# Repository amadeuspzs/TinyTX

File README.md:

# TinyTX

This repo picks up on the work on Nathan Chantrell, sadly R.I.P. late 2020.

* Nathan's website [via Archive.org](https://web.archive.org/web/20150202220320/http://nathan.chantrell.net/tinytx-wireless-sensor/)
* Nathan's [TinyTX repo on Github](https://github.com/nathanchantrell/TinyTX)
* Archive of [TinyTX3 hardware](TinyTX3/)

## Motivation

Since Nathan created TinyTX, both chips have evolved:

1. RFM12B -> [RFM69](https://www.hoperf.com/modules/rf_transceiver/index.html)
2. ATtiny84 -> ATtiny 0,1 series e.g. [ATtiny1614](https://ww1.microchip.com/downloads/en/DeviceDoc/ATtiny1614-16-17-DataSheet-DS40002204A.pdf)

## High level design

This project will create a TinyTX4 using:

1. RFM69HW
2. ATtiny1614
3. lowpowerlab's [RFM69](https://github.com/lowpowerlab/rfm69) library

And release all hardware and software in this repository.

## Radio module choice

Here is a comparison of [RFM69](https://www.hoperf.com/modules/rf_transceiver/index.html) variants:

Variant|Output (dBm)|Pinout|Size (mm)
---|---|---|---
RFM69[**W**](https://www.hoperf.com/modules/rf_transceiver/RFM69W.html)|13|RFM69W|19.7 x 16
RFM69[**CW**](https://www.hoperf.com/modules/rf_transceiver/RFM69C.html)|13|RFM69CW|16 x 16
RFM69[**HW**](https://www.hoperf.com/%20modules/rf_transceiver/RFM69HW.html)|20|RFM69W|19.7 x 16
RFM69[**HCW**](https://www.hoperf.com/modules/rf_transceiver/RFM69HCW.html)|20|RFM69HCW|16 x 16

i.e. RFM69W and RFM69HW share pinout, but are larger (19.7&nbsp;x&nbsp;16)mm vs the RFMCW and RFMHCW (16&nbsp;x&nbsp;16)mm.

For interoperability between normal and high-power modules, we'll go with the **RFM69(H)W** modules.

## Hardware versions

* [TinyTX4](hardware/TinyTX4) (monopole and SMA)

## Software

See [software](software/) page.

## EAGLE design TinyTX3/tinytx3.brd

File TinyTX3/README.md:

# TinyTX3 Hardware

Archived from Nathan's website [via Archive.org](https://web.archive.org/web/20150202220320/http://nathan.chantrell.net/tinytx-wireless-sensor/):

## Schematic

* [Eagle file](tinytx3.sch)
* [KiCad files](KiCad/)

## Board

* [Eagle file](tinytx3.brd)
* [KiCad files](KiCad/)

## Case

* [OpenSCAD](TinyTX_Case.scad)

## Implementation

### Pinout

### AA implementation

### LiPo implementation

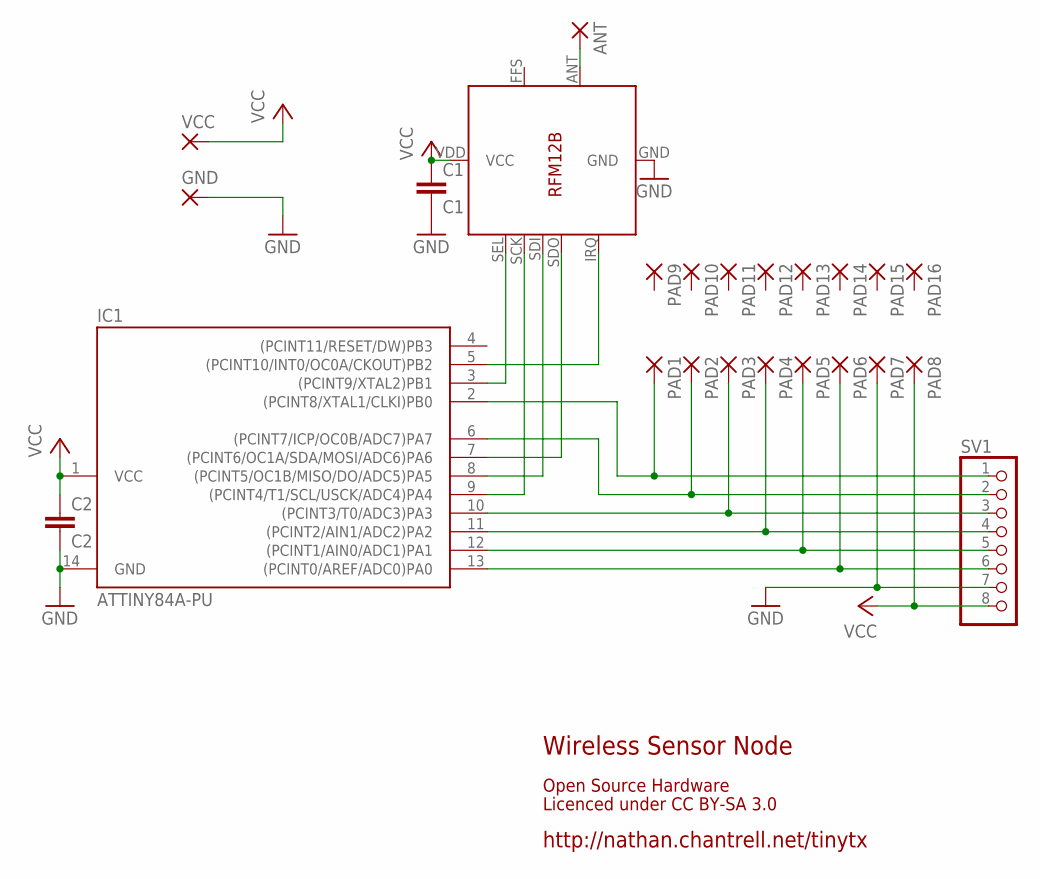
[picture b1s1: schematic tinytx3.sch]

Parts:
ANT: 1,6/0,8
C1: C1; C025-025X050
C2: C2; C025-025X050
GND: 2,15/1,0
IC1: ATTINY84A-PU; DIL14
PAD1, PAD2, PAD3, PAD4, PAD5, PAD6, PAD7, PAD8, PAD9, PAD10, PAD11, PAD12, PAD13, PAD14, PAD15, PAD16: 1,6/0,9
SV1: PINHD-1X8; 1X08
U$1: RFM12B
VCC: 2,15/1,0

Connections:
GND: C1.2, C2.2, GND.1, IC1.14 (GND), PAD7.1, SV1.7, U$1.GND
unnamed: IC1.3 ((PCINT9/XTAL2)PB1), U$1.SEL
unnamed: IC1.5 ((PCINT10/INT0/OC0A/CKOUT)PB2), U$1.IRQ
unnamed: IC1.8 ((PCINT5/OC1B/MISO/DO/ADC5)PA5), U$1.SDI
unnamed: IC1.7 ((PCINT6/OC1A/SDA/MOSI/ADC6)PA6), U$1.SDO
unnamed: ANT.1, U$1.ANT
unnamed: IC1.9 ((PCINT4/T1/SCL/USCK/ADC4)PA4), U$1.SCK
unnamed: IC1.6 ((PCINT7/ICP/OC0B/ADC7)PA7), PAD2.1, SV1.2
unnamed: IC1.13 ((PCINT0/AREF/ADC0)PA0), PAD6.1, SV1.6
unnamed: IC1.12 ((PCINT1/AIN0/ADC1)PA1), PAD5.1, SV1.5
unnamed: IC1.2 ((PCINT8/XTAL1/CLKI)PB0), PAD1.1, SV1.1
unnamed: IC1.11 ((PCINT2/AIN1/ADC2)PA2), PAD4.1, SV1.4
unnamed: IC1.10 ((PCINT3/T0/ADC3)PA3), PAD3.1, SV1.3
VCC: C1.1, C2.1, IC1.1 (VCC), PAD8.1, SV1.8, U$1.VDD (VCC), VCC.1

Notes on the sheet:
http://nathan.chantrell.net/tinytx
Wireless Sensor Node
Licenced under CC BY-SA 3.0
Open Source Hardware

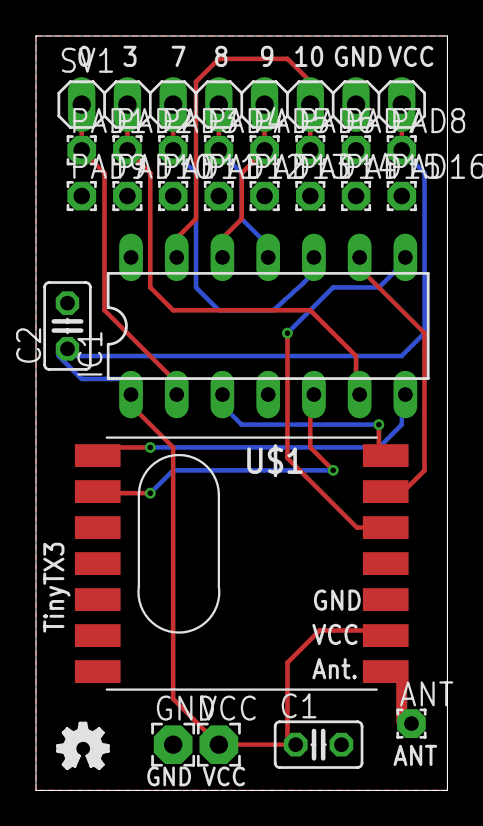
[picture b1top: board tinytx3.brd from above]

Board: 2 copper layers, 22.9 x 41.9 mm, 25 parts (0 on the bottom side), 14 nets.

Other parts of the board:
U$2: OSHW_FILLX100_NOTEXT

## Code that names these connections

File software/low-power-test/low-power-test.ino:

// go to sleep with lowest power mode, for profiling
// burn bootloader with brown out detection disabled
// set clock to 1MHz

// benchmarks June 1 2022, TinyTX4 no connections:
// 30uA sleep
// 1.1mA wake

#include <avr/sleep.h>
#include <util/delay.h>
#include <RFM69.h>      // https://github.com/lowpowerlab/rfm69
#include <SPI.h>

#define NODEID      99   // id of this device
#define NETWORKID   1   // your network id
#define GATEWAYID   1   // id of your gateway
#define FREQUENCY     RF69_433MHZ
#define IS_RFM69HW_HCW  //uncomment only for RFM69HW/HCW! Leave out if you have RFM69W/CW! See https://lowpowerlab.com/guide/moteino/transceivers/

RFM69 radio;

// setup for the RTC
void RTC_init(void) {
  // initialise RTC:
  RTC.CLKSEL = RTC_CLKSEL_INT1K_gc;         // 1.024kHz Internal Ultra-Low-Power Oscillator (from OSCULP32K)
  while (RTC.STATUS > 0 || RTC.PITSTATUS);  // Wait for all registers to be synchronised
  RTC.PITINTCTRL = RTC_PI_bm;               // PIT Interrupt: enabled
  RTC.PITCTRLA = RTC_PERIOD_CYC1024_gc      // Num cycles between interrupt. RTC Clock Cycles 1024, resulting in 1024/1024Hz = every 1 seconds
  | RTC_PITEN_bm;                           // enable PIT counter
}

// interrupt subroutine, runs when PIT wakes up
ISR(RTC_PIT_vect) {
  RTC.PITINTFLAGS = RTC_PI_bm;          // clear interrupt flag by writing '1' (required)
}

void setup() {

//   define unused pins as PULLUP to save power
  pinMode(PIN_PA0, INPUT_PULLUP);
  //pinMode(PIN_PA1, INPUT_PULLUP); // MOSI
  //pinMode(PIN_PA2, INPUT_PULLUP); // MISO
  //pinMode(PIN_PA3, INPUT_PULLUP); // SCK
  //pinMode(PIN_PA4, INPUT_PULLUP); // NSS
  pinMode(PIN_PA5, INPUT_PULLUP);
  //pinMode(PIN_PA6, INPUT_PULLUP); // DIO0
  pinMode(PIN_PA7, INPUT_PULLUP);
  pinMode(PIN_PB0, INPUT_PULLUP);
  pinMode(PIN_PB1, INPUT_PULLUP);
  pinMode(PIN_PB2, INPUT_PULLUP);
  pinMode(PIN_PB3, INPUT_PULLUP);

  radio.initialize(FREQUENCY,NODEID,NETWORKID);
  #ifdef IS_RFM69HW_HCW
    radio.setHighPower(); //must include this only for RFM69HW/HCW!
  #endif

  radio.sleep();  // sleep radio

  RTC_init();                           // initialise the RTC timer
  set_sleep_mode(SLEEP_MODE_PWR_DOWN);  // set sleep mode to POWER DOWN mode
  sleep_enable();                       // enable sleep mode, but not going to sleep yet
  sei();                                // enable interrupts
}

void loop() {
  _delay_ms(1000); // 1000ms delay for power measurements
  sleep_cpu();
}

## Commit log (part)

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2021-03-01 Add TinyTX3 hardware
2021-03-09 Kicad
2021-03-09 Remove kicad collateral
2021-03-09 TinyTX4
2021-03-09 Add TinyTX4 docs
2021-03-09 Add front page link
2021-03-09 Add 3d graphic
2021-03-21 Update info
2021-03-23 Add test sketch
2022-04-03 Add printed version
2022-04-03 Add latest version
2022-04-03 Add docs
2022-04-07 Update heartbeat sketch
2022-05-08 Add radio sleep
2022-05-08 fix: revert to 1s on 1s off
2022-05-08 feat: add ping with sleep mode
2022-05-08 update HC-SR04
2022-05-08 docs: update links to software
2022-05-08 docs: link to software page
2022-06-05 feat: add working HC-SR04 code
2022-06-05 docs: add benchmark values
2022-06-06 fix: rename sketch file
2026-06-11 feat: updated to latest
2026-06-11 chore: build
2026-06-15 feat: sen0300
2026-06-21 wip: sen0300 low power with heartbeat
